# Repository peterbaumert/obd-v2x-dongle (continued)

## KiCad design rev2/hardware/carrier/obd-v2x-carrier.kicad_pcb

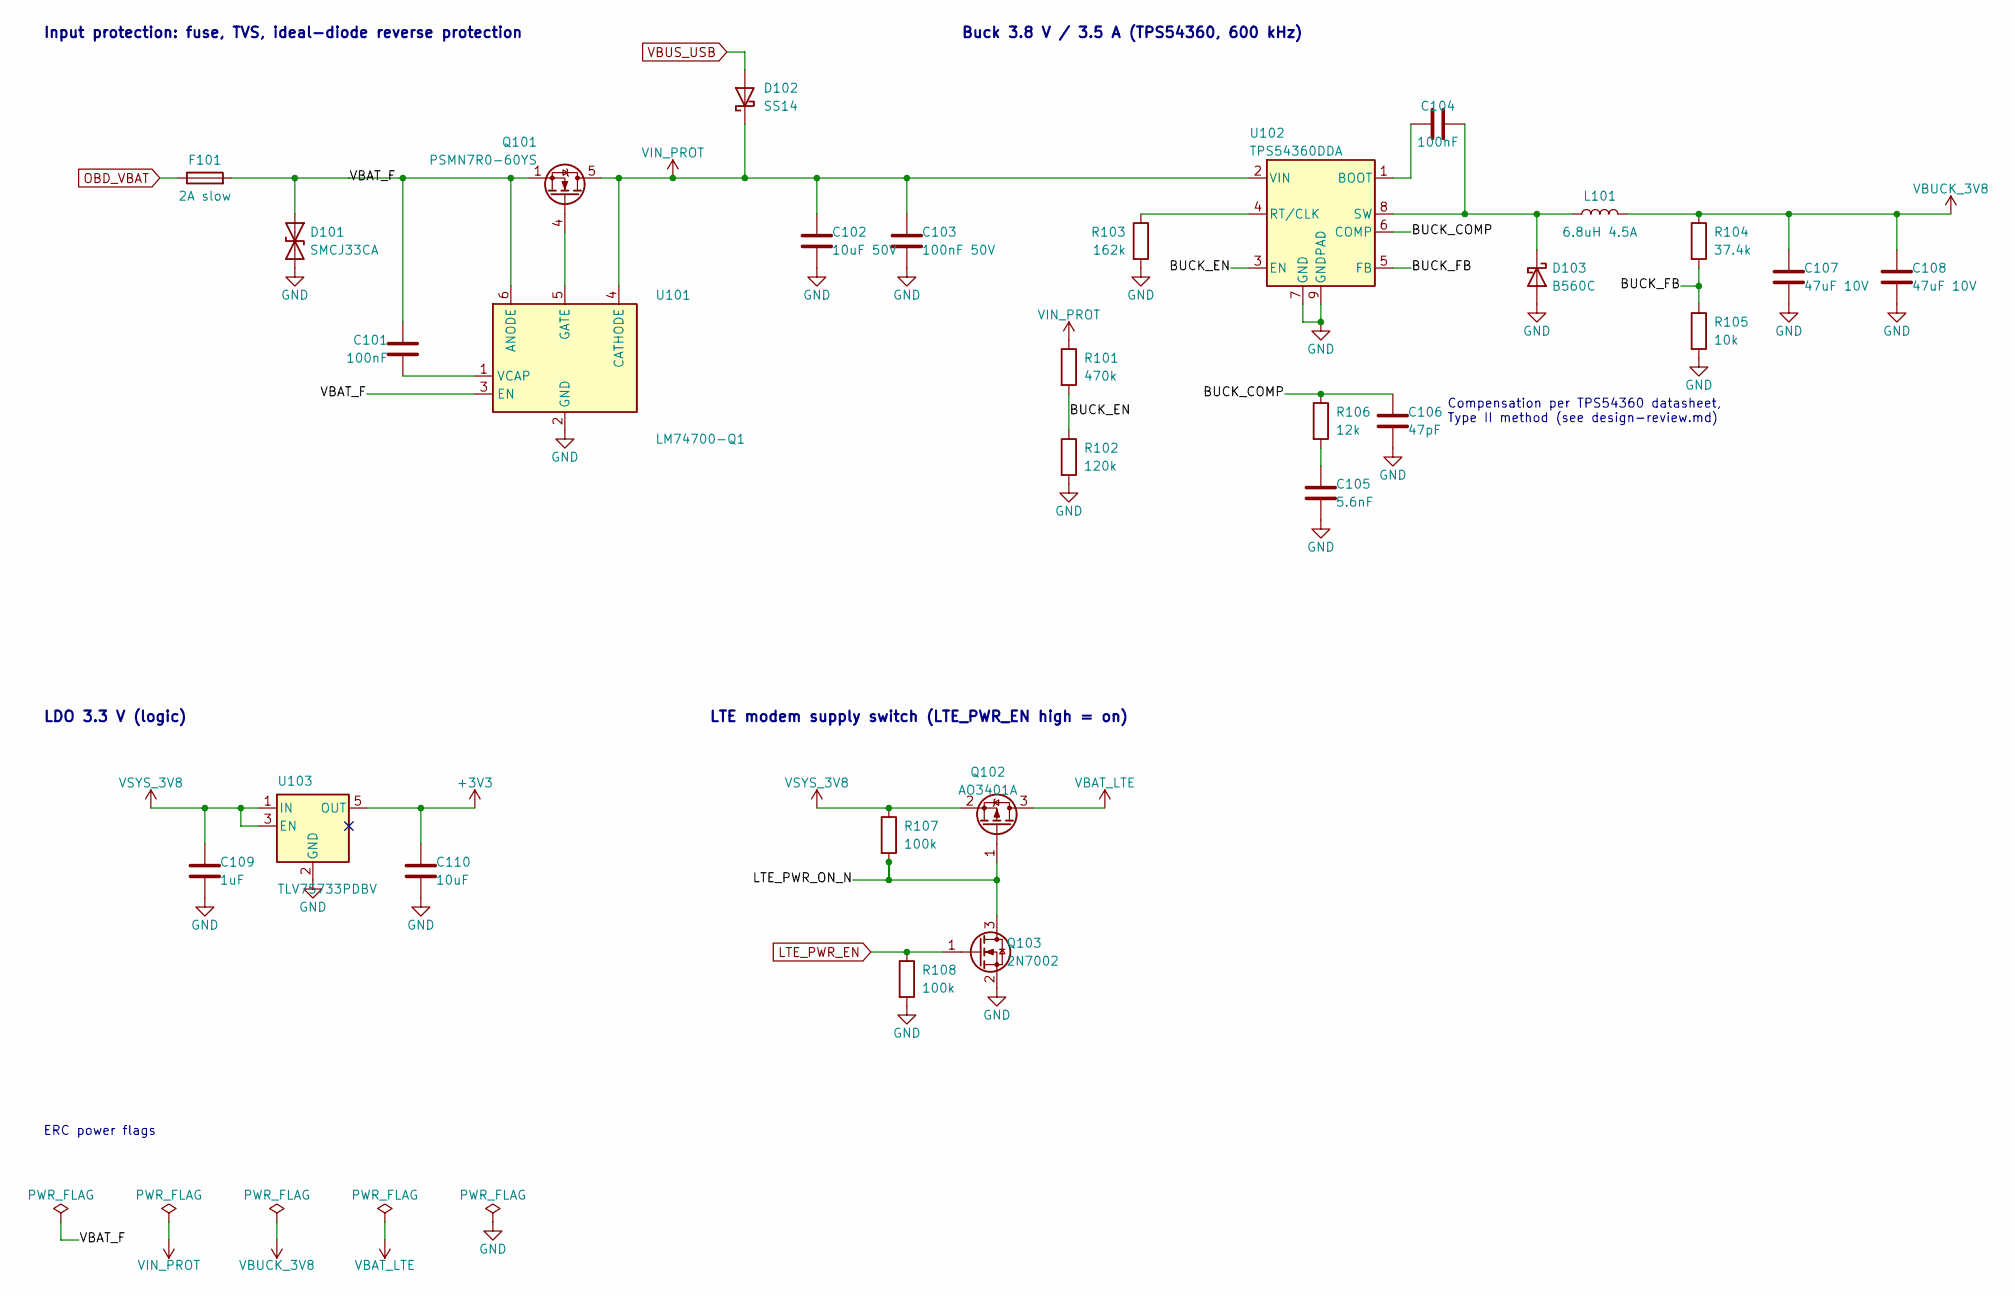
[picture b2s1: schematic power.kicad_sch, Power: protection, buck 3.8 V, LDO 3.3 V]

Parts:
C101, C104: 100nF; C_0603_1608Metric
C102: 10uF 50V; C_1210_3225Metric
C103: 100nF 50V; C_0603_1608Metric
C105: 5.6nF; C_0603_1608Metric
C106: 47pF; C_0603_1608Metric
C107, C108: 47uF 10V; C_1210_3225Metric
C109: 1uF; C_0603_1608Metric
C110: 10uF; C_0805_2012Metric
D101: SMCJ33CA; D_SMC; MPN SMCJ33CA; LCSC C310048
D102: SS14; D_SMA; MPN SS14; LCSC C2480
D103: B560C; D_SMC; MPN B560C-13-F; LCSC C85100
F101: 2A slow; Fuse_1206_3216Metric; MPN 0466002.NRHF; LCSC C3105
L101: 6.8uH 4.5A; L_Sunlord_MWSA0605S; MPN MWSA0605S-6R8MT; LCSC C408466
Q101: PSMN7R0-60YS; LFPAK56; MPN PSMN7R0-60YS,115; LCSC C478143
Q102: AO3401A; SOT-23; MPN AO3401A; LCSC C15127
Q103: 2N7002; SOT-23; MPN 2N7002; LCSC C8545
R101: 470k; R_0603_1608Metric
R102: 120k; R_0603_1608Metric
R103: 162k; R_0603_1608Metric
R104: 37.4k; R_0603_1608Metric
R105: 10k; R_0603_1608Metric
R106: 12k; R_0603_1608Metric
R107, R108: 100k; R_0603_1608Metric
U101: LM74700-Q1; SOT-23-6; MPN LM74700QDBVRQ1; LCSC C2941042
U102: TPS54360DDA; TI_SO-PowerPAD-8; MPN TPS54360DDAR; LCSC C44377
U103: TLV75733PDBV; SOT-23-5; MPN TLV75733PDBVR; LCSC C485517

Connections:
+3V3: C110.1, U103.5 (OUT); also elsewhere on the board
/Power/BUCK_COMP: C106.1, R106.1, U102.6 (COMP)
/Power/BUCK_EN: R101.2, R102.1, U102.3 (EN)
/Power/BUCK_FB: R104.2, R105.1, U102.5 (FB)
/Power/LTE_PWR_ON_N: Q102.1 (G), Q103.3 (D), R107.2
/Power/VBAT_F: C101.2, D101.1 (A1), F101.2, Q101.1 (S), Q101.2 (S), Q101.3 (S), U101.3 (EN), U101.6 (ANODE)
GND: C102.2, C103.2, C105.2, C106.2, C107.2, C108.2, C109.2, C110.2, D101.2 (A2), D103.2 (A), Q103.2 (S), R102.2, R103.2, R105.2, R108.2, U101.2 (GND), U102.7 (GND), U102.9 (GNDPAD), U103.2 (GND); also elsewhere on the board
LTE_PWR_EN: Q103.1 (G), R108.1; also elsewhere on the board
unnamed: C105.1, R106.2
unnamed: C104.2, D103.1 (K), L101.1, U102.8 (SW)
unnamed: Q101.4 (G), U101.5 (GATE)
unnamed: C101.1, U101.1 (VCAP)
unnamed: C104.1, U102.1 (BOOT)
unnamed: R103.1, U102.4 (RT/CLK)
OBD_VBAT: F101.1; also elsewhere on the board
VBAT_LTE: Q102.3 (D); also elsewhere on the board
VBUCK_3V8: C107.1, C108.1, L101.2, R104.1; also elsewhere on the board
VBUS_USB: D102.2 (A); also elsewhere on the board
VIN_PROT: C102.1, C103.1, D102.1 (K), Q101.5 (D), R101.1, U101.4 (CATHODE), U102.2 (VIN); also elsewhere on the board
VSYS_3V8: C109.1, Q102.2 (S), R107.1, U103.1 (IN), U103.3 (EN); also elsewhere on the board

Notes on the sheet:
LTE modem supply switch (LTE_PWR_EN high = on)
ERC power flags
Compensation per TPS54360 datasheet, Type II method (see design-review.md)
LDO 3.3 V (logic)
Buck 3.8 V / 3.5 A (TPS54360, 600 kHz)
Input protection: fuse, TVS, ideal-diode reverse protection

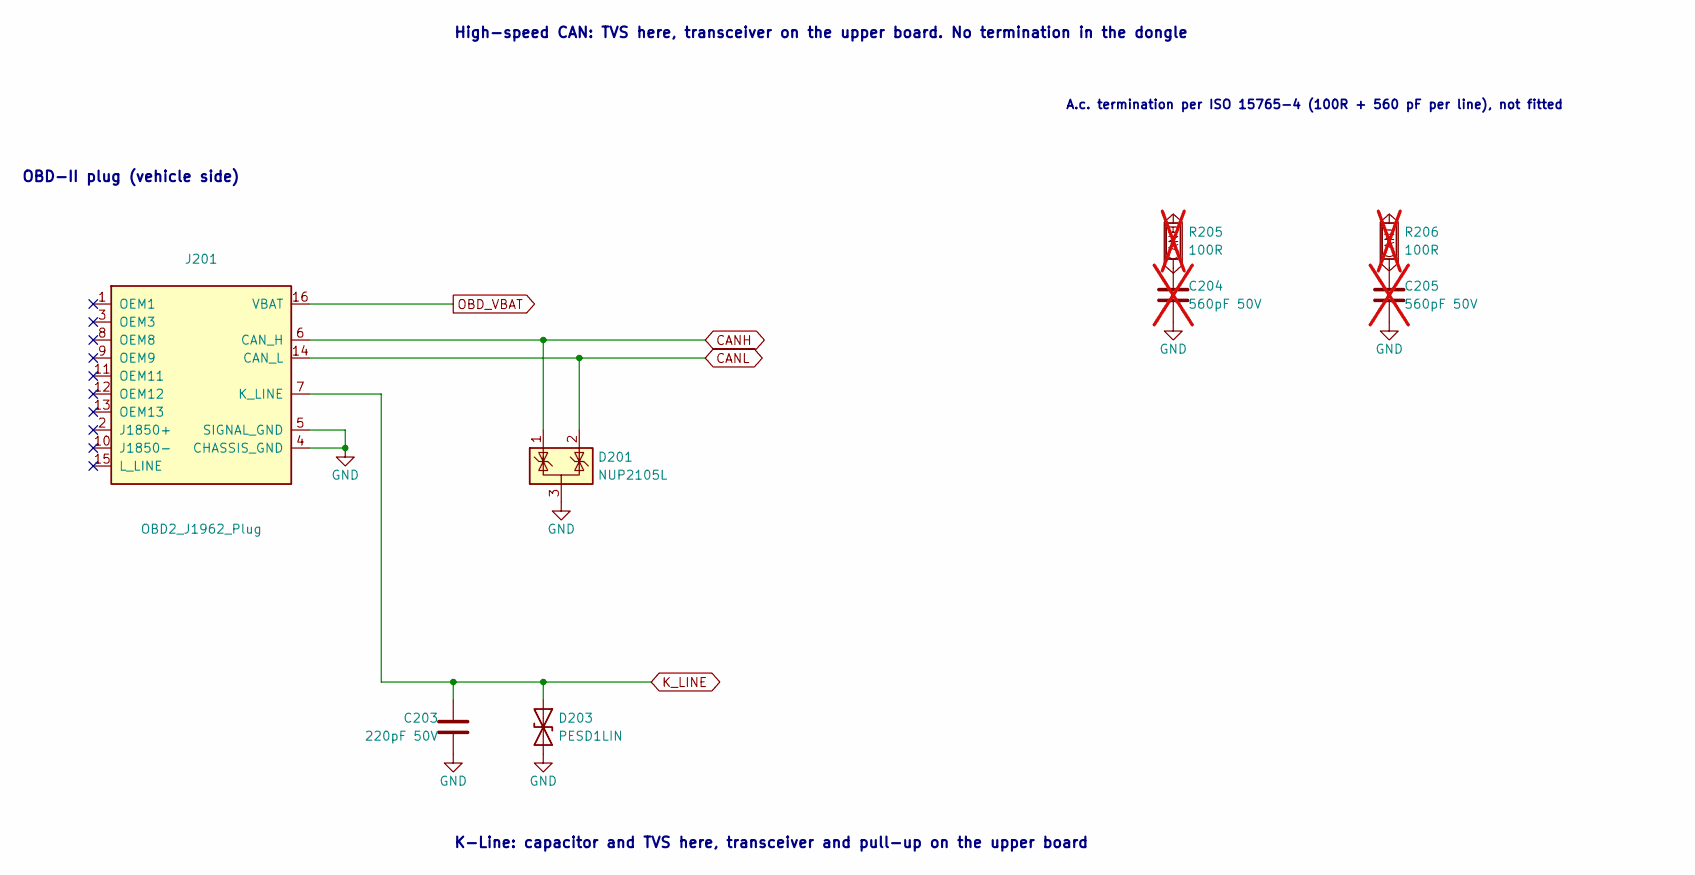
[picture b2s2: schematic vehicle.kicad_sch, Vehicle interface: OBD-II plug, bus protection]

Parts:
C203: 220pF 50V; C_0603_1608Metric
C204, C205: 560pF 50V; C_0603_1608Metric; not fitted
D201: NUP2105L; SOT-23; MPN SZNUP2105LT1G; LCSC C233494
D203: PESD1LIN; D_SOD-323; MPN PESD1LIN,115; LCSC C58901
J201: OBD2_J1962_Plug; OBD2_J1962_Plug_PCB; MPN CR-PG001 (OBD2 male 90deg PCB, hand-fit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
R205, R206: 100R; R_0603_1608Metric; not fitted

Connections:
CANH: D201.1 (K), J201.6 (CAN_H), R205.1; also elsewhere on the board
CANL: D201.2 (K), J201.14 (CAN_L), R206.1; also elsewhere on the board
GND: C203.2, C204.2, C205.2, D201.3 (A), D203.2 (A2), J201.4 (CHASSIS_GND), J201.5 (SIGNAL_GND); also elsewhere on the board
K_LINE: C203.1, D203.1 (A1), J201.7 (K_LINE); also elsewhere on the board
unnamed: C204.1, R205.2
unnamed: C205.1, R206.2
OBD_VBAT: J201.16 (VBAT); also elsewhere on the board

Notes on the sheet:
High-speed CAN: TVS here, transceiver on the upper board. No termination in the dongle
OBD-II plug (vehicle side)
A.c. termination per ISO 15765-4 (100R + 560 pF per line), not fitted
K-Line: capacitor and TVS here, transceiver and pull-up on the upper board

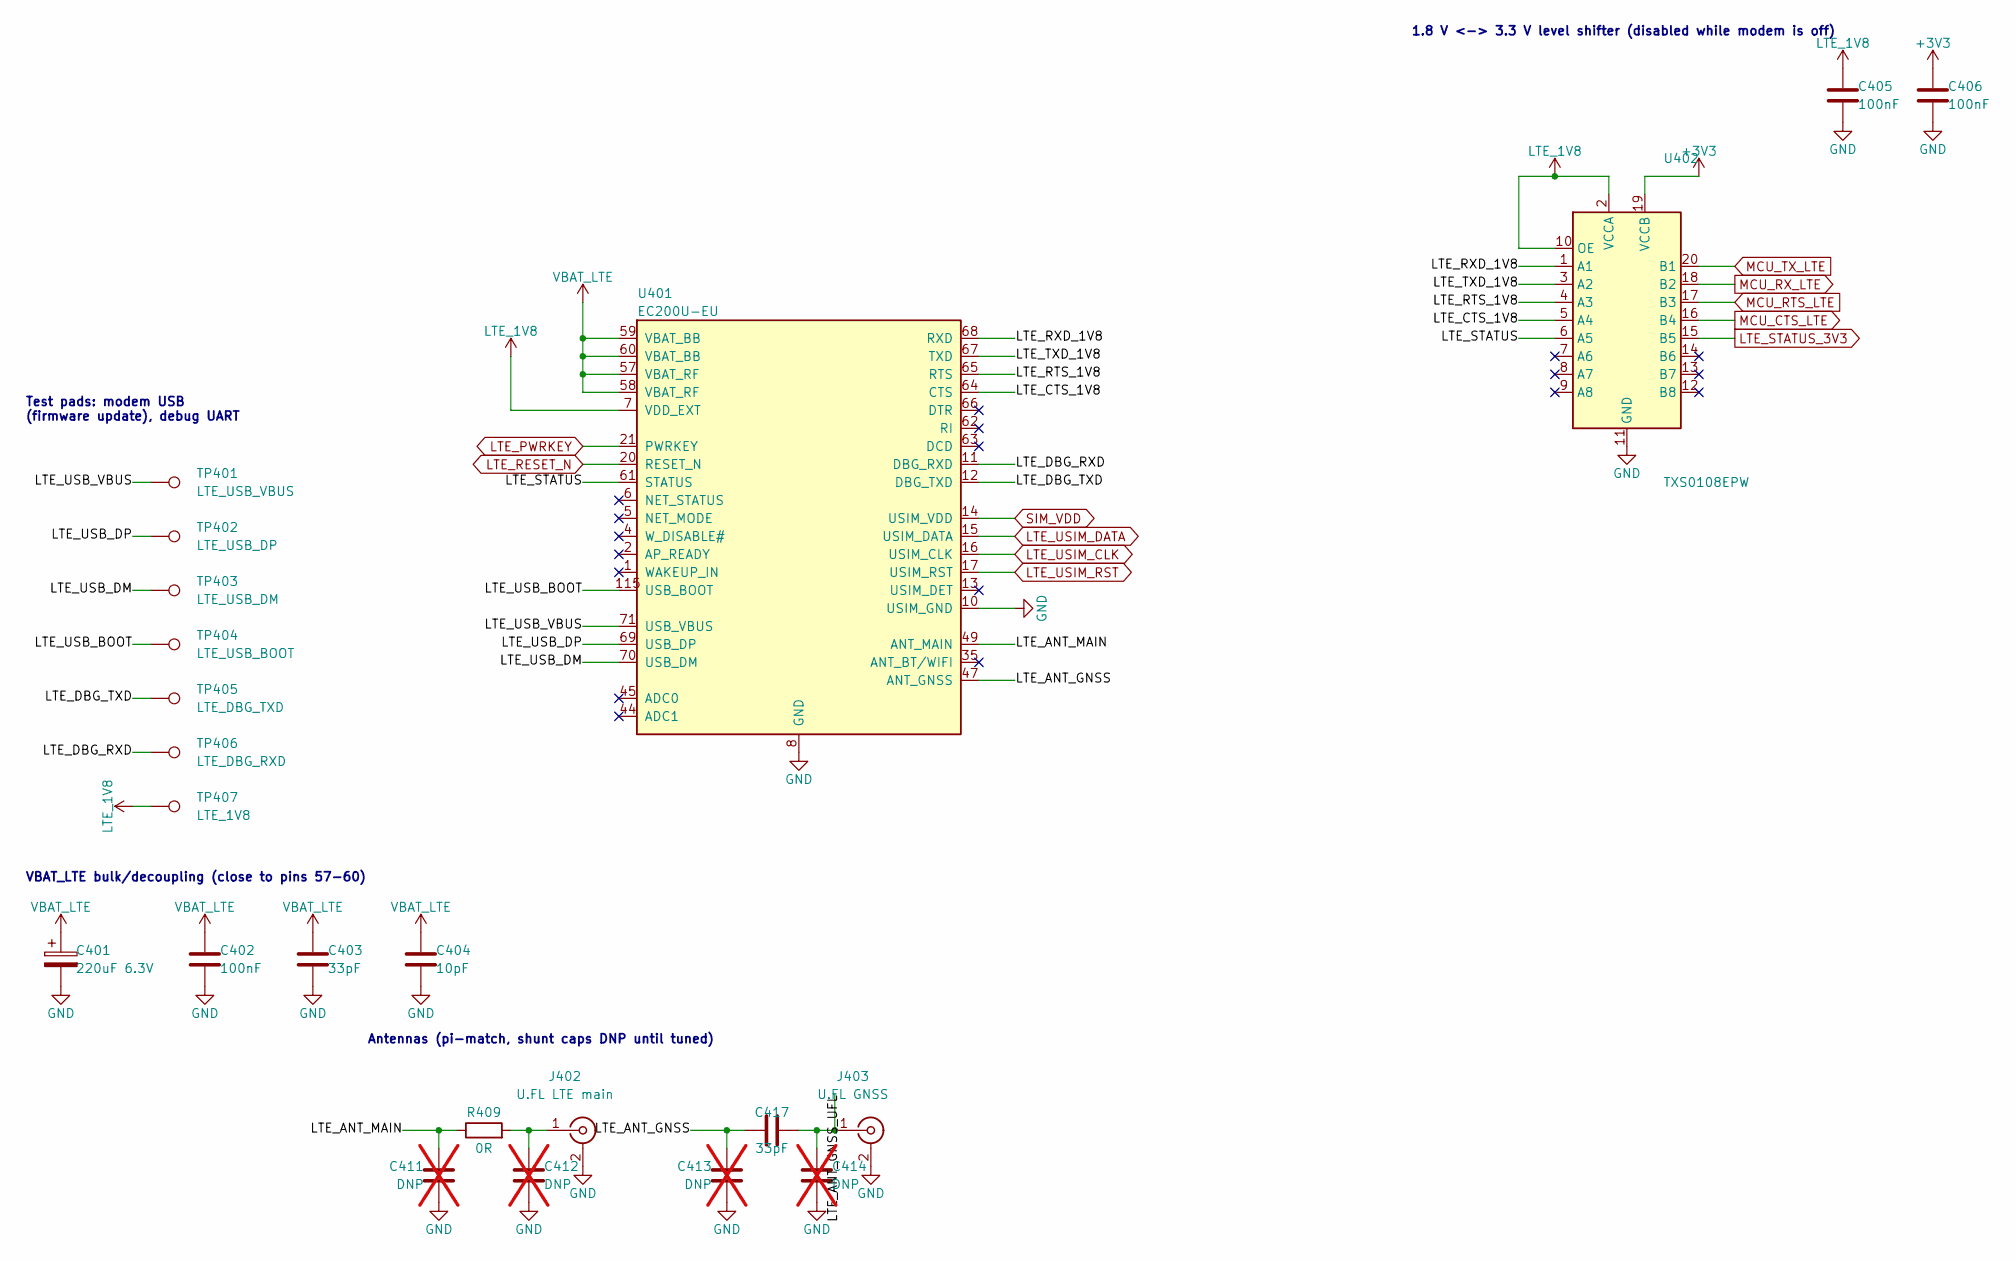
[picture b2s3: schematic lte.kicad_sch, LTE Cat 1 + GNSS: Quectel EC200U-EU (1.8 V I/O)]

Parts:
C401: 220uF 6.3V; CP_EIA-7343-20_Kemet-V; MPN T520V227M006ATE015; LCSC C696810
C402, C405, C406: 100nF; C_0603_1608Metric
C403: 33pF; C_0402_1005Metric
C404: 10pF; C_0402_1005Metric
C411, C412, C413, C414: DNP; C_0402_1005Metric; not fitted
C417: 33pF; C_0402_1005Metric; MPN 0402CG330J500NT; LCSC C1562
J402: U.FL LTE main; U.FL_Hirose_U.FL-R-SMT-1_Vertical; MPN U.FL-R-SMT-1(10); LCSC C88373
J403: U.FL GNSS; U.FL_Hirose_U.FL-R-SMT-1_Vertical; MPN U.FL-R-SMT-1(10); LCSC C88373
R409: 0R; R_0402_1005Metric
TP401: LTE_USB_VBUS; TestPoint_Pad_D1.0mm
TP402: LTE_USB_DP; TestPoint_Pad_D1.0mm
TP403: LTE_USB_DM; TestPoint_Pad_D1.0mm
TP404: LTE_USB_BOOT; TestPoint_Pad_D1.0mm
TP405: LTE_DBG_TXD; TestPoint_Pad_D1.0mm
TP406: LTE_DBG_RXD; TestPoint_Pad_D1.0mm
TP407: LTE_1V8; TestPoint_Pad_D1.0mm
U401: EC200U-EU; Quectel_EC200U; MPN EC200UEUAA-N05-SGNSA; LCSC C2942341
U402: TXS0108EPW; TSSOP-20_4.4x6.5mm_P0.65mm; MPN TXS0108EPWR; LCSC C17206

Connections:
+3V3: C406.1, U402.19 (VCCB); also elsewhere on the board
/LTE + GNSS (EC200U)/LTE_ANT_GNSS: C413.1, C417.1, U401.47 (ANT_GNSS)
/LTE + GNSS (EC200U)/LTE_ANT_GNSS_UFL: C414.1, C417.2, J403.1 (In)
/LTE + GNSS (EC200U)/LTE_ANT_MAIN: C411.1, R409.1, U401.49 (ANT_MAIN)
/LTE + GNSS (EC200U)/LTE_CTS_1V8: U401.64 (CTS), U402.5 (A4)
/LTE + GNSS (EC200U)/LTE_DBG_RXD: TP406.1, U401.11 (DBG_RXD)
/LTE + GNSS (EC200U)/LTE_DBG_TXD: TP405.1, U401.12 (DBG_TXD)
/LTE + GNSS (EC200U)/LTE_RTS_1V8: U401.65 (RTS), U402.4 (A3)
/LTE + GNSS (EC200U)/LTE_RXD_1V8: U401.68 (RXD), U402.1 (A1)
/LTE + GNSS (EC200U)/LTE_STATUS: U401.61 (STATUS), U402.6 (A5)
/LTE + GNSS (EC200U)/LTE_TXD_1V8: U401.67 (TXD), U402.3 (A2)
/LTE + GNSS (EC200U)/LTE_USB_BOOT: TP404.1, U401.115 (USB_BOOT)
/LTE + GNSS (EC200U)/LTE_USB_DM: TP403.1, U401.70 (USB_DM)
/LTE + GNSS (EC200U)/LTE_USB_DP: TP402.1, U401.69 (USB_DP)
/LTE + GNSS (EC200U)/LTE_USB_VBUS: TP401.1, U401.71 (USB_VBUS)
GND: C401.2, C402.2, C403.2, C404.2, C405.2, C406.2, C411.2, C412.2, C413.2, C414.2, J402.2 (Ext), J403.2 (Ext), U401.8 (GND), U401.9 (GND), U401.10 (USIM_GND), U401.19 (GND), U401.22 (GND), U401.36 (GND), U401.46 (GND), U401.48 (GND), U401.50 (GND), U401.51 (GND), U401.52 (GND), U401.53 (GND), U401.54 (GND), U401.56 (GND), U401.72 (GND), U401.76 (GND), U401.85 (GND), U401.86 (GND), U401.87 (GND), U401.88 (GND), U401.89 (GND), U401.90 (GND), U401.91 (GND), U401.92 (GND), U401.93 (GND), U401.94 (GND), U401.95 (GND), U401.96 (GND), U401.97 (GND), U401.98 (GND), U401.99 (GND), U401.100 (GND), U401.101 (GND), U401.102 (GND), U401.103 (GND), U401.104 (GND), U401.105 (GND), U401.106 (GND), U401.107 (GND), U401.108 (GND), U401.109 (GND), U401.110 (GND), U401.111 (GND), U401.112 (GND), U402.11 (GND); also elsewhere on the board
LTE_1V8: C405.1, TP407.1, U401.7 (VDD_EXT), U402.2 (VCCA), U402.10 (OE)
LTE_PWRKEY: U401.21 (PWRKEY); also elsewhere on the board
LTE_RESET_N: U401.20 (RESET_N); also elsewhere on the board
LTE_STATUS_3V3: U402.15 (B5); also elsewhere on the board
LTE_USIM_CLK: U401.16 (USIM_CLK); also elsewhere on the board
LTE_USIM_DATA: U401.15 (USIM_DATA); also elsewhere on the board
LTE_USIM_RST: U401.17 (USIM_RST); also elsewhere on the board
MCU_CTS_LTE: U402.16 (B4); also elsewhere on the board
MCU_RTS_LTE: U402.17 (B3); also elsewhere on the board
MCU_RX_LTE: U402.18 (B2); also elsewhere on the board
MCU_TX_LTE: U402.20 (B1); also elsewhere on the board
unnamed: C412.1, J402.1 (In), R409.2
SIM_VDD: U401.14 (USIM_VDD); also elsewhere on the board
VBAT_LTE: C401.1, C402.1, C403.1, C404.1, U401.57 (VBAT_RF), U401.58 (VBAT_RF), U401.59 (VBAT_BB), U401.60 (VBAT_BB); also elsewhere on the board

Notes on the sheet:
Test pads: modem USB (firmware update), debug UART
VBAT_LTE bulk/decoupling (close to pins 57-60)
1.8 V <-> 3.3 V level shifter (disabled while modem is off)
Antennas (pi-match, shunt caps DNP until tuned)

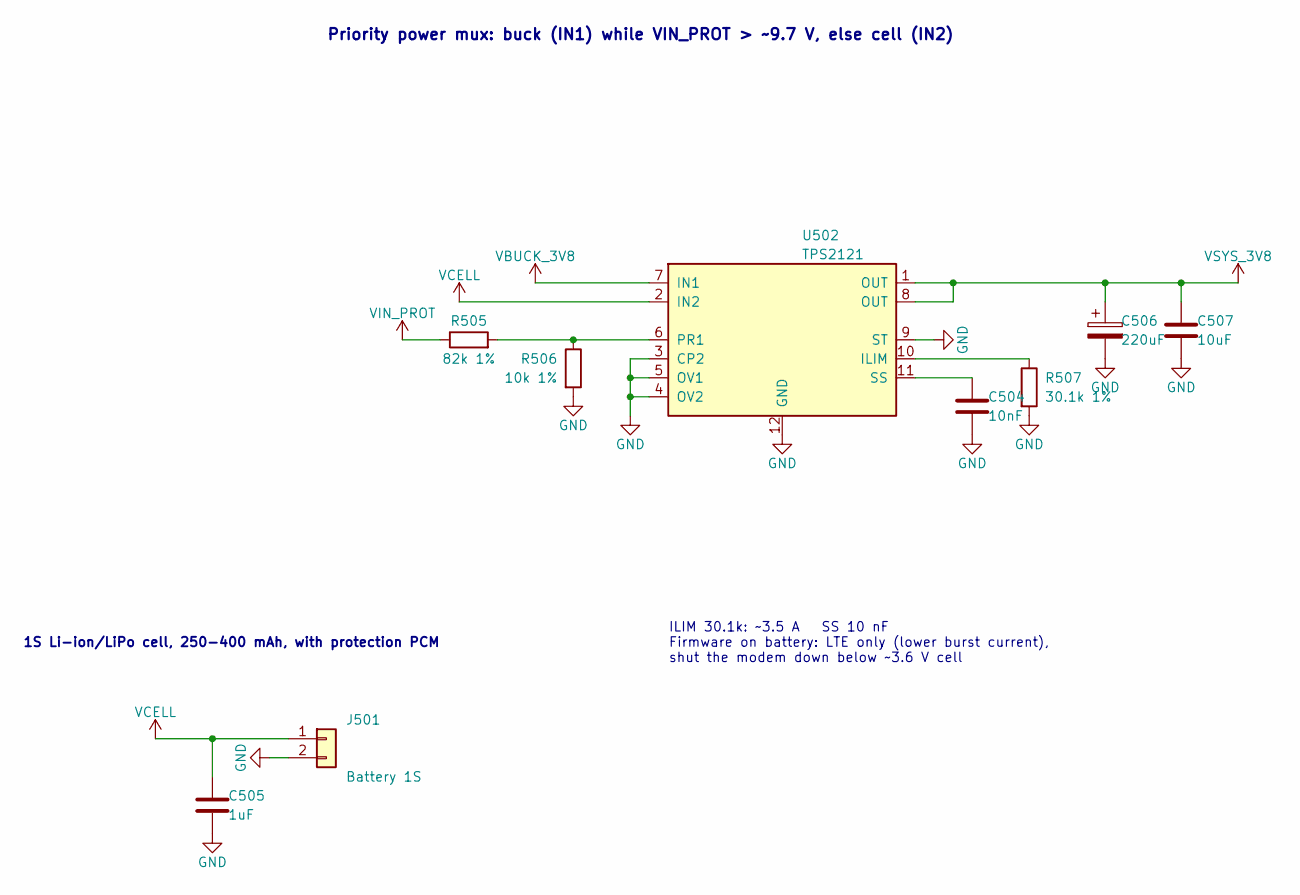
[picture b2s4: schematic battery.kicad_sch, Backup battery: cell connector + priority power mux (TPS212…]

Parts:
C504: 10nF; C_0603_1608Metric
C505: 1uF; C_0603_1608Metric
C506: 220uF; CP_EIA-7343-31_Kemet-D; MPN T495D227K006ATE100; LCSC C2798131
C507: 10uF; C_0805_2012Metric
J501: Battery 1S; JST_PH_S2B-PH-SM4-TB_1x02-1MP_P2.00mm_Horizontal; MPN S2B-PH-SM4-TB(LF)(SN); LCSC C295747
R505: 82k 1%; R_0603_1608Metric
R506: 10k 1%; R_0603_1608Metric
R507: 30.1k 1%; R_0603_1608Metric
U502: TPS2121; Texas_VQFN-HR-12_2x2.5mm_P0.5mm; MPN TPS2121RUXR; LCSC C485916

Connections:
GND: C504.2, C505.2, C506.2, C507.2, J501.2, R506.2, R507.2, U502.3 (CP2), U502.4 (OV2), U502.5 (OV1), U502.9 (ST), U502.12 (GND); also elsewhere on the board
unnamed: R507.1, U502.10 (ILIM)
unnamed: R505.2, R506.1, U502.6 (PR1)
unnamed: C504.1, U502.11 (SS)
VBUCK_3V8: U502.7 (IN1); also elsewhere on the board
VCELL: C505.1, J501.1, U502.2 (IN2); also elsewhere on the board
VIN_PROT: R505.1; also elsewhere on the board
VSYS_3V8: C506.1, C507.1, U502.1 (OUT), U502.8 (OUT); also elsewhere on the board

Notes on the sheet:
ILIM 30.1k: ~3.5 A SS 10 nF Firmware on battery: LTE only (lower burst current), shut the modem down below ~3.6 V cell
1S Li-ion/LiPo cell, 250-400 mAh, with protection PCM
Priority power mux: buck (IN1) while VIN_PROT > ~9.7 V, else cell (IN2)

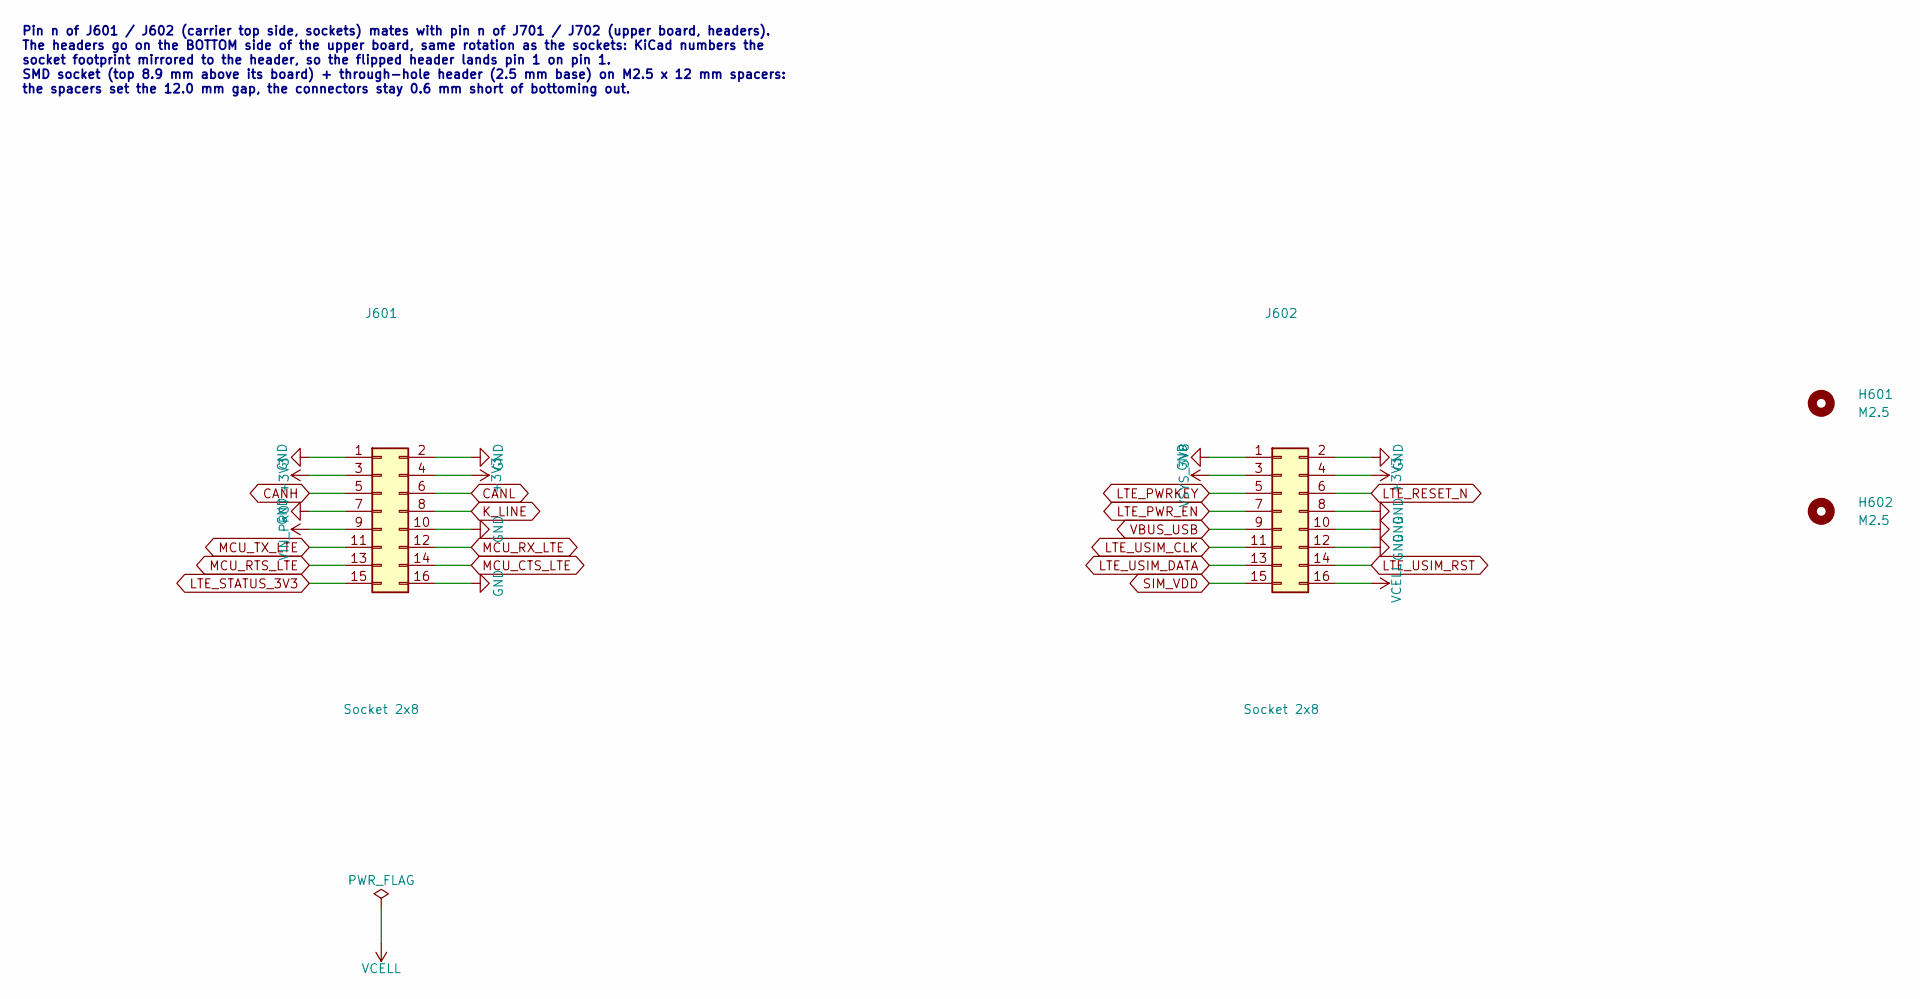
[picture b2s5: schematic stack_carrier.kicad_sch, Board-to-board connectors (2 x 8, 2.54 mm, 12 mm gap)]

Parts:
H601, H602: M2.5; MountingHole_2.7mm_M2.5
J601, J602: Socket 2x8; PinSocket_2x08_P2.54mm_Vertical_SMD; MPN HX PM2.54-2x8P TP; LCSC C41427537

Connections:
+3V3: J601.3, J601.4, J602.4; also elsewhere on the board
CANH: J601.5; also elsewhere on the board
CANL: J601.6; also elsewhere on the board
GND: J601.1, J601.2, J601.7, J601.10, J601.16, J602.1, J602.2, J602.8, J602.10, J602.12; also elsewhere on the board
K_LINE: J601.8; also elsewhere on the board
LTE_PWRKEY: J602.5; also elsewhere on the board
LTE_PWR_EN: J602.7; also elsewhere on the board
LTE_RESET_N: J602.6; also elsewhere on the board
LTE_STATUS_3V3: J601.15; also elsewhere on the board
LTE_USIM_CLK: J602.11; also elsewhere on the board
LTE_USIM_DATA: J602.13; also elsewhere on the board
LTE_USIM_RST: J602.14; also elsewhere on the board
MCU_CTS_LTE: J601.14; also elsewhere on the board
MCU_RTS_LTE: J601.13; also elsewhere on the board
MCU_RX_LTE: J601.12; also elsewhere on the board
MCU_TX_LTE: J601.11; also elsewhere on the board
SIM_VDD: J602.15; also elsewhere on the board
VBUS_USB: J602.9; also elsewhere on the board
VCELL: J602.16; also elsewhere on the board
VIN_PROT: J601.9; also elsewhere on the board
VSYS_3V8: J602.3; also elsewhere on the board

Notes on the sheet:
Pin n of J601 / J602 (carrier top side, sockets) mates with pin n of J701 / J702 (upper board, headers). The headers go on the BOTTOM side of the upper board, same rotation as the sockets: KiCad numbers the socket footprint mirrored to the header, so the flipped header lands pin 1 on pin 1. SMD soc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

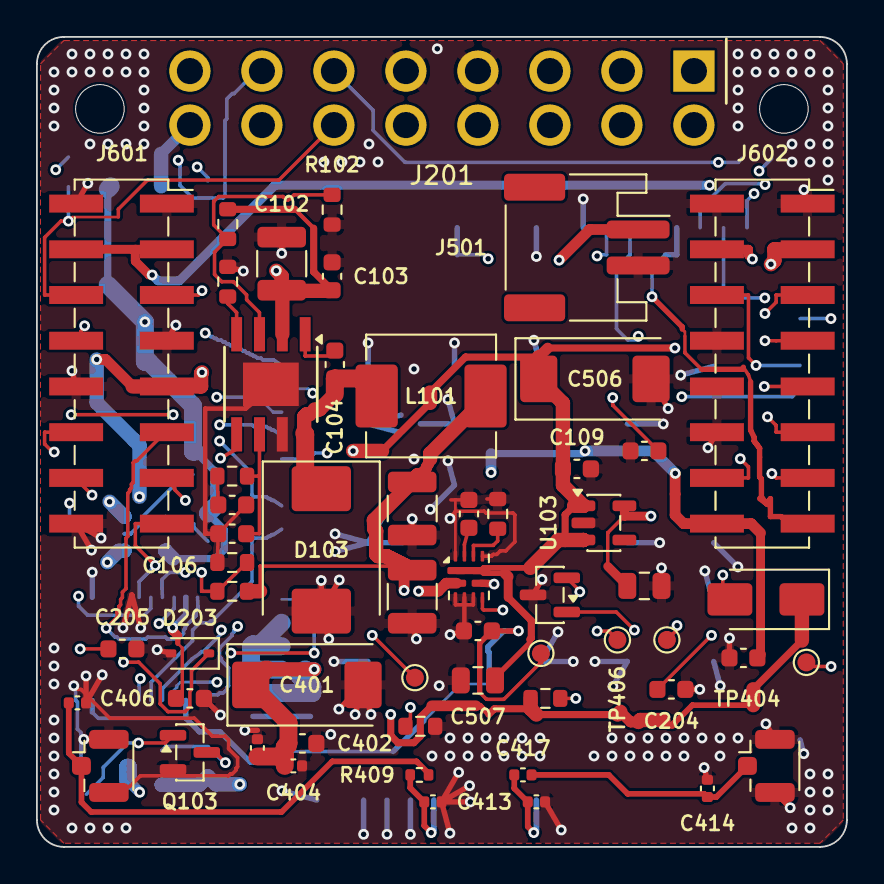
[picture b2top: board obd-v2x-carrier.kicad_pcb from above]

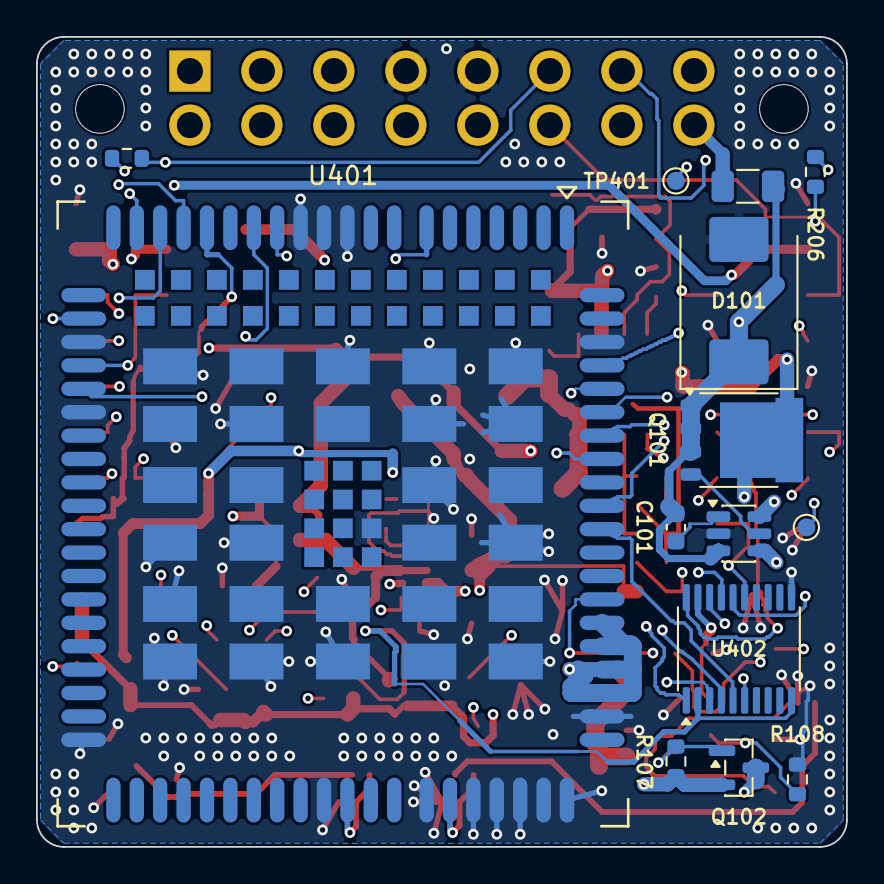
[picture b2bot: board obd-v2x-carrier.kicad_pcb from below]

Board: 4 copper layers, 45.0 x 45.0 mm, 73 parts (14 on the bottom side), 56 nets.

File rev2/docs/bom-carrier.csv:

"Reference","Value","Footprint","MPN","Manufacturer","LCSC","Qty","DNP"
"C101,C104,C402,C405,C406","100nF","Capacitor_SMD:C_0603_1608Metric","","","","5",""
"C102","10uF 50V","Capacitor_SMD:C_1210_3225Metric","","","","1",""
"C103","100nF 50V","Capacitor_SMD:C_0603_1608Metric","","","","1",""
"C105","5.6nF","Capacitor_SMD:C_0603_1608Metric","","","","1",""
"C106","47pF","Capacitor_SMD:C_0603_1608Metric","","","","1",""
"C107,C108","47uF 10V","Capacitor_SMD:C_1210_3225Metric","","","","2",""
"C109,C505","1uF","Capacitor_SMD:C_0603_1608Metric","","","","2",""
"C110,C507","10uF","Capacitor_SMD:C_0805_2012Metric","","","","2",""
"C203","220pF 50V","Capacitor_SMD:C_0603_1608Metric","","","","1",""
"C204,C205","560pF 50V","Capacitor_SMD:C_0603_1608Metric","","","","2","DNP"
"C401","220uF 6.3V","Capacitor_Tantalum_SMD:CP_EIA-7343-20_Kemet-V","T520V227M006ATE015","KEMET","C696810","1",""
"C403","33pF","Capacitor_SMD:C_0402_1005Metric","","","","1",""
"C404","10pF","Capacitor_SMD:C_0402_1005Metric","","","","1",""
"C411,C412,C413,C414","DNP","Capacitor_SMD:C_0402_1005Metric","","","","4","DNP"
"C417","33pF","Capacitor_SMD:C_0402_1005Metric","0402CG330J500NT","FH","C1562","1",""
"C504","10nF","Capacitor_SMD:C_0603_1608Metric","","","","1",""
"C506","220uF","Capacitor_Tantalum_SMD:CP_EIA-7343-31_Kemet-D","T495D227K006ATE100","KEMET","C2798131","1",""
"D101","SMCJ33CA","Diode_SMD:D_SMC","SMCJ33CA","Littelfuse","C310048","1",""
"D102","SS14","Diode_SMD:D_SMA","SS14","MDD","C2480","1",""
"D103","B560C","Diode_SMD:D_SMC","B560C-13-F","Diodes Inc","C85100","1",""
"D201","NUP2105L","Package_TO_SOT_SMD:SOT-23","SZNUP2105LT1G","onsemi","C233494","1",""
"D203","PESD1LIN","Diode_SMD:D_SOD-323","PESD1LIN,115","Nexperia","C58901","1",""
"F101","2A slow","Fuse:Fuse_1206_3216Metric","0466002.NRHF","Littelfuse","C3105","1",""
"H601,H602","M2.5","MountingHole:MountingHole_2.7mm_M2.5","","","","2",""
"J201","OBD2_J1962_Plug","obd-v2x:OBD2_J1962_Plug_PCB","CR-PG001 (OBD2 male 90deg PCB, hand-fitted)","Jiatel or equivalent","","1",""
"J402","U.FL LTE main","Connector_Coaxial:U.FL_Hirose_U.FL-R-SMT-1_Vertical","U.FL-R-SMT-1(10)","Hirose","C88373","1",""
"J403","U.FL GNSS","Connector_Coaxial:U.FL_Hirose_U.FL-R-SMT-1_Vertical","U.FL-R-SMT-1(10)","Hirose","C88373","1",""
"J501","Battery 1S","Connector_JST:JST_PH_S2B-PH-SM4-TB_1x02-1MP_P2.00mm_Horizontal","S2B-PH-SM4-TB(LF)(SN)","JST","C295747","1",""
"J601,J602","Socket 2x8","Connector_PinSocket_2.54mm:PinSocket_2x08_P2.54mm_Vertical_SMD","HX PM2.54-2x8P TP","Hanxia","C41427537","2",""
"L101","6.8uH 4.5A","Inductor_SMD:L_Sunlord_MWSA0605S","MWSA0605S-6R8MT","Sunlord","C408466","1",""
"Q101","PSMN7R0-60YS","Package_TO_SOT_SMD:LFPAK56","PSMN7R0-60YS,115","Nexperia","C478143","1",""
"Q102","AO3401A","Package_TO_SOT_SMD:SOT-23","AO3401A","AOS","C15127","1",""
"Q103","2N7002","Package_TO_SOT_SMD:SOT-23","2N7002","onsemi","C8545","1",""
"R101","470k","Resistor_SMD:R_0603_1608Metric","","","","1",""
"R102","120k","Resistor_SMD:R_0603_1608Metric","","","","1",""
"R103","162k","Resistor_SMD:R_0603_1608Metric","","","","1",""
"R104","37.4k","Resistor_SMD:R_0603_1608Metric","","","","1",""
"R105","10k","Resistor_SMD:R_0603_1608Metric","","","","1",""
"R106","12k","Resistor_SMD:R_0603_1608Metric","","","","1",""
"R107,R108","100k","Resistor_SMD:R_0603_1608Metric","","","","2",""
"R205,R206","100R","Resistor_SMD:R_0603_1608Metric","","","","2","DNP"
"R409","0R","Resistor_SMD:R_0402_1005Metric","","","","1",""
"R505","82k 1%","Resistor_SMD:R_0603_1608Metric","","","","1",""
"R506","10k 1%","Resistor_SMD:R_0603_1608Metric","","","","1",""
"R507","30.1k 1%","Resistor_SMD:R_0603_1608Metric","","","","1",""
"TP401","LTE_USB_VBUS","TestPoint:TestPoint_Pad_D1.0mm","","","","1",""
"TP402","LTE_USB_DP","TestPoint:TestPoint_Pad_D1.0mm","","","","1",""
"TP403","LTE_USB_DM","TestPoint:TestPoint_Pad_D1.0mm","","","","1",""
"TP404","LTE_USB_BOOT","TestPoint:TestPoint_Pad_D1.0mm","","","","1",""
"TP405","LTE_DBG_TXD","TestPoint:TestPoint_Pad_D1.0mm","","","","1",""
"TP406","LTE_DBG_RXD","TestPoint:TestPoint_Pad_D1.0mm","","","","1",""
"TP407","LTE_1V8","TestPoint:TestPoint_Pad_D1.0mm","","","","1",""
"U101","LM74700-Q1","Package_TO_SOT_SMD:SOT-23-6","LM74700QDBVRQ1","TI","C2941042","1",""
"U102","TPS54360DDA","Package_SO:TI_SO-PowerPAD-8","TPS54360DDAR","TI","C44377","1",""
"U103","TLV75733PDBV","Package_TO_SOT_SMD:SOT-23-5","TLV75733PDBVR","TI","C485517","1",""
"U401","EC200U-EU","obd-v2x:Quectel_EC200U","EC200UEUAA-N05-SGNSA","Quectel","C2942341","1",""
"U402","TXS0108EPW","Package_SO:TSSOP-20_4.4x6.5mm_P0.65mm","TXS0108EPWR","TI","C17206","1",""
"U502","TPS2121","Package_DFN_QFN:Texas_VQFN-HR-12_2x2.5mm_P0.5mm","TPS2121RUXR","Texas Instruments","C485916","1",""
